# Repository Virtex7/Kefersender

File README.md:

# Kefersender
FM Transmitter auf Basis des MMR70-Moduls und des darauf befindlichen Alps 603A UKW-Sendemoduls

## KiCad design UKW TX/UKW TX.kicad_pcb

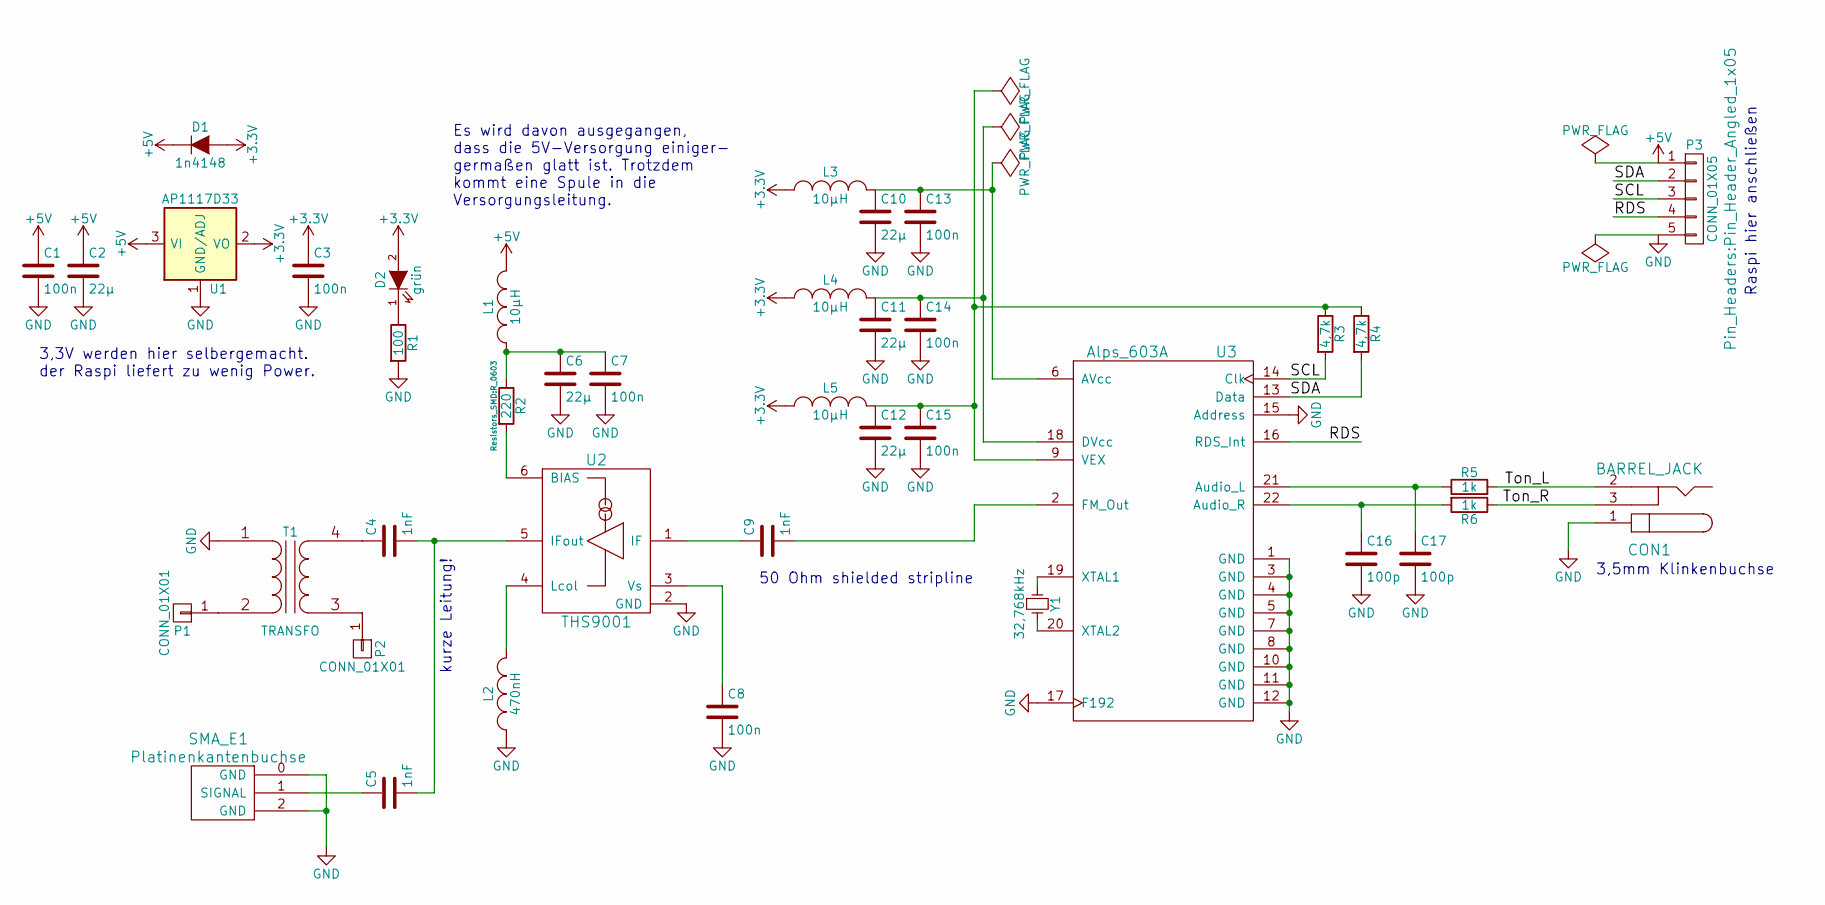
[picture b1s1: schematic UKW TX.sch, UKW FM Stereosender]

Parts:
C1, C3, C7, C8, C13, C14, C15: 100n; C_0402
C2, C6, C10, C11, C12: 22µ; C_0805
C4, C5, C9: 1nF; C_0805
C16, C17: 100p; C_0402
CON1: BARREL_JACK
D1: 1n4148; Diode-MiniMELF_Standard
D2: grün; LED-0603
L1, L3, L4, L5: 10µH; R_0805
L2: 470nH; R_1206
P1, P2: CONN_01X01; Pin_Header_Angled_1x01
P3: CONN_01X05; Pin_Header_Angled_1x05
R1: 100; C_0603
R2: 220; R_0603
R3, R4: 4,7k; C_0603
R5, R6: 1k; R_0402
SMA_E1: Platinenkantenbuchse; SMA_EDGE
T1: TRANSFO; AT224-1A
U1: AP1117D33; SOT89-3_Housing
U2: THS9001; SOT-23-6
U3: Alps_603A
Y1: 32,768kHz; R_1206

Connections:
+3V3: C3.1, D1.2 (A), D2.2 (A), L3.1, L4.1, L5.1, U1.2 (VO)
+5V: C1.1, C2.1, D1.1 (K), L1.2, P3.1, U1.3 (VI)
/RDS: P3.4, U3.16 (RDS_Int)
/SCL: P3.3, R3.2, U3.14 (Clk)
/SDA: P3.2, R4.2, U3.13 (Data)
/Ton_L: CON1.2, R5.2
/Ton_R: CON1.3, R6.1
GND: C1.2, C2.2, C3.2, C6.2, C7.2, C8.2, C10.2, C11.2, C12.2, C13.2, C14.2, C15.2, C16.2, C17.2, CON1.1, L2.1, P3.5, R1.2, SMA_E1.0 (GND), SMA_E1.2 (GND), T1.1 (AA), U1.1 (GND/ADJ), U2.2 (GND), U3.1 (GND), U3.3 (GND), U3.4 (GND), U3.5 (GND), U3.7 (GND), U3.8 (GND), U3.10 (GND), U3.11 (GND), U3.12 (GND), U3.15 (Address), U3.17 (F192)
unnamed: C4.1, T1.4 (SB)
unnamed: C4.2, C5.2, U2.5 (IFout)
unnamed: C5.1, SMA_E1.1 (SIGNAL)
unnamed: C6.1, C7.1, L1.1, R2.1
unnamed: C8.1, U2.3 (Vs)
unnamed: C9.1, U2.1 (IF)
unnamed: C9.2, U3.2 (FM_Out)
unnamed: C10.1, C13.1, L3.2, U3.6 (AVcc)
unnamed: C11.1, C14.1, L4.2, U3.18 (DVcc)
unnamed: C12.1, C15.1, L5.2, R3.1, R4.1, U3.9 (VEX)
unnamed: C16.1, R6.2, U3.22 (Audio_R)
unnamed: C17.1, R5.1, U3.21 (Audio_L)
unnamed: D2.1 (K), R1.1
unnamed: L2.2, U2.4 (Lcol)
unnamed: P1.1, T1.2 (AB)
unnamed: P2.1, T1.3 (SA)
unnamed: R2.2, U2.6 (BIAS)
unnamed: U3.19 (XTAL1), Y1.1
unnamed: U3.20 (XTAL2), Y1.2

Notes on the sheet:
3,3V werden hier selbergemacht. der Raspi liefert zu wenig Power.
50 Ohm shielded stripline
3,5mm Klinkenbuchse
kurze Leitung!
Es wird davon ausgegangen, dass die 5V-Versorgung einiger- germaßen glatt ist. Trotzdem kommt eine Spule in die Versorgungsleitung.
Raspi hier anschließen

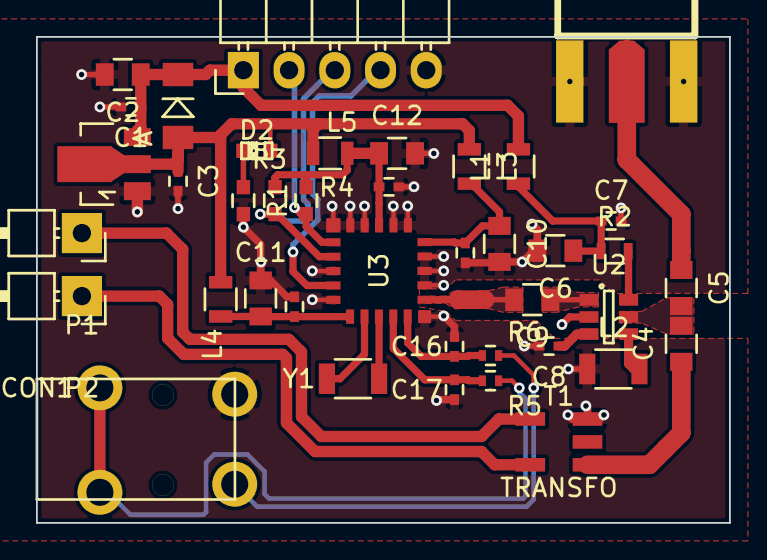
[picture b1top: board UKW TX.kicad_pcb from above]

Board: 2 copper layers, 38.5 x 27.0 mm, 40 parts (0 on the bottom side), 27 nets.

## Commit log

2015-06-19 ein paar Daten und die Software
2015-06-19 Schaltplan für den Kefersender angefangen
2015-06-26 layout quasi fertig.
2015-06-26 platine fertig.
2015-06-27 platine fertig - incl anpassleitung
